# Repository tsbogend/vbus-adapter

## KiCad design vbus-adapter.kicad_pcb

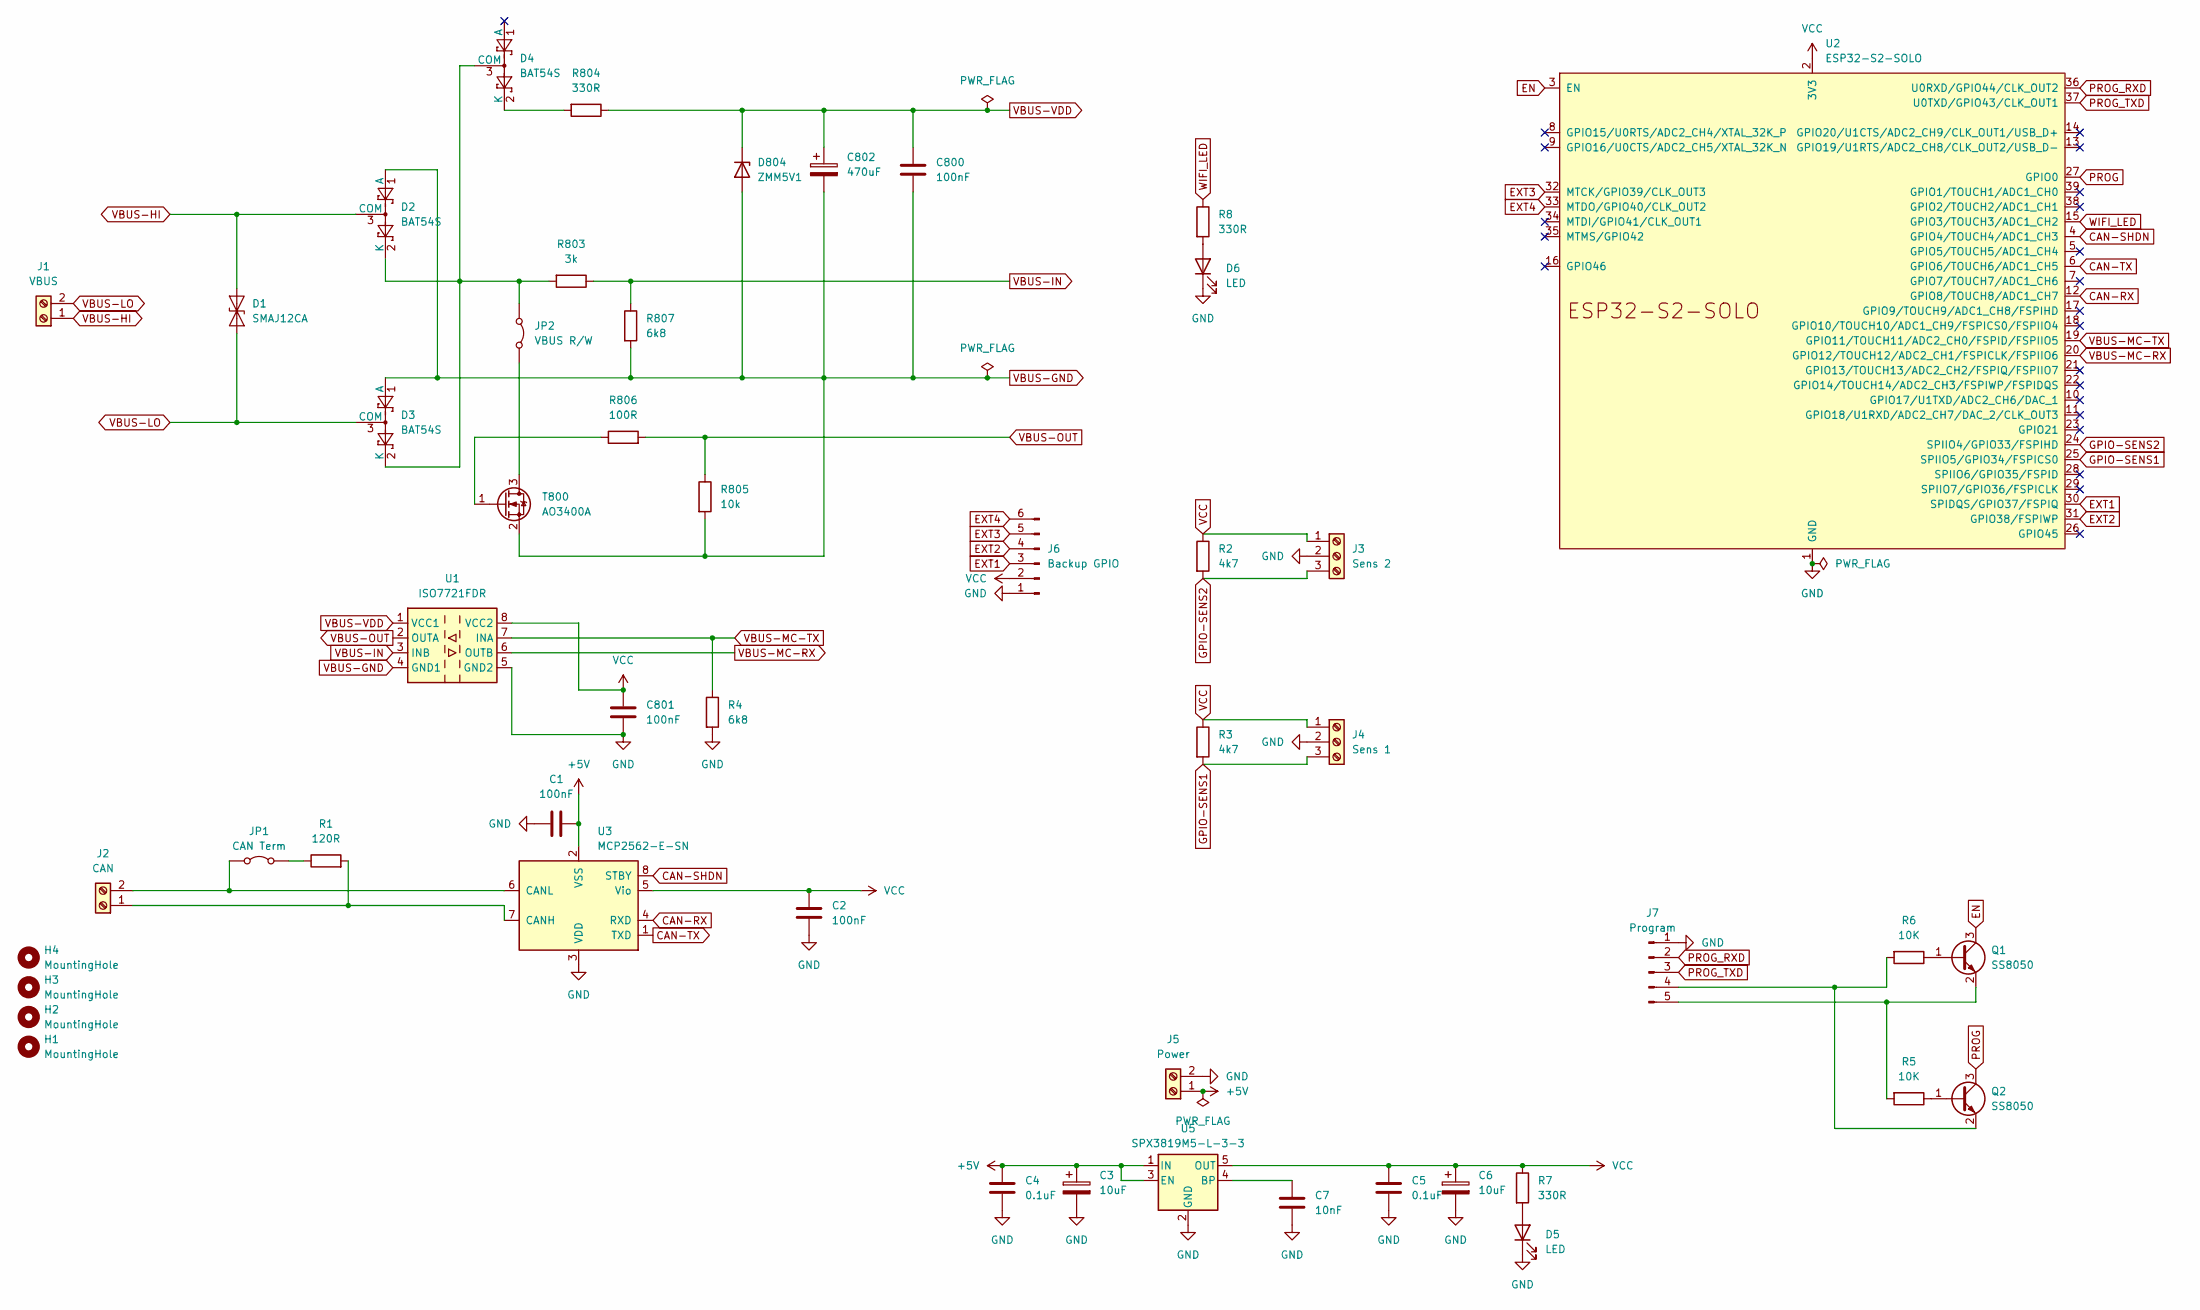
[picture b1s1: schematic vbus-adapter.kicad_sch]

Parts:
C1, C2, C800, C801: 100nF; C_0805_2012Metric_Pad1.18x1.45mm_HandSolder
C3, C6: 10uF; C_0805_2012Metric_Pad1.18x1.45mm_HandSolder
C4, C5: 0.1uF; C_0805_2012Metric_Pad1.18x1.45mm_HandSolder
C7: 10nF; C_0805_2012Metric_Pad1.18x1.45mm_HandSolder
C802: 470uF; CP_Elec_4x3.9
D1: SMAJ12CA; D_SMA
D2, D3, D4: BAT54S; SOT-23
D5, D6: LED; LED_0805_2012Metric_Pad1.15x1.40mm_HandSolder
D804: ZMM5V1; D_MiniMELF
H1, H2, H3, H4: MountingHole; MountingHole_3.2mm_M3_DIN965_Pad
J1: VBUS; TerminalBlock_Phoenix_MPT-0,5-2-2.54_1x02_P2.54mm_Horizontal
J2: CAN; TerminalBlock_Phoenix_MPT-0,5-2-2.54_1x02_P2.54mm_Horizontal
J3: Sens 2; TerminalBlock_Phoenix_MPT-0,5-3-2.54_1x03_P2.54mm_Horizontal
J4: Sens 1; TerminalBlock_Phoenix_MPT-0,5-3-2.54_1x03_P2.54mm_Horizontal
J5: Power; TerminalBlock_Phoenix_MPT-0,5-2-2.54_1x02_P2.54mm_Horizontal
J6: Backup GPIO; PinHeader_1x06_P2.54mm_Vertical
J7: Program; PinHeader_1x05_P2.54mm_Vertical
JP1: CAN Term; PinHeader_1x02_P2.54mm_Vertical
JP2: VBUS R/W; PinHeader_1x02_P2.54mm_Vertical
Q1, Q2: SS8050; SOT-23
R1: 120R; R_0805_2012Metric_Pad1.20x1.40mm_HandSolder
R2, R3: 4k7; R_0805_2012Metric_Pad1.20x1.40mm_HandSolder
R4, R807: 6k8; R_0805_2012Metric_Pad1.20x1.40mm_HandSolder
R5, R6: 10K; R_0805_2012Metric_Pad1.20x1.40mm_HandSolder
R7, R8, R804: 330R; R_0805_2012Metric_Pad1.20x1.40mm_HandSolder
R803: 3k; R_0805_2012Metric_Pad1.20x1.40mm_HandSolder
R805: 10k; R_0805_2012Metric_Pad1.20x1.40mm_HandSolder
R806: 100R; R_0805_2012Metric_Pad1.20x1.40mm_HandSolder
T800: AO3400A; SOT-23
U1: ISO7721FDR; SOIC-8_3.9x4.9mm_P1.27mm
U2: ESP32-S2-SOLO
U3: MCP2562-E-SN; SOIC-8_3.9x4.9mm_P1.27mm
U5: SPX3819M5-L-3-3; SOT-23-5

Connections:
+5V: C1.1, C3.1, C4.1, J5.1, U3.2 (VSS), U5.1 (IN), U5.3 (EN)
CAN-RX: U2.12 (GPIO8/TOUCH8/ADC1_CH7), U3.4 (RXD)
CAN-SHDN: U2.4 (GPIO4/TOUCH4/ADC1_CH3), U3.8 (STBY)
CAN-TX: U2.6 (GPIO6/TOUCH6/ADC1_CH5), U3.1 (TXD)
EN: Q1.3 (C), U2.3 (EN)
EXT1: J6.3, U2.30 (SPIDQS/GPIO37/FSPIQ)
EXT2: J6.4, U2.31 (GPIO38/FSPIWP)
EXT3: J6.5, U2.32 (MTCK/GPIO39/CLK_OUT3)
EXT4: J6.6, U2.33 (MTDO/GPIO40/CLK_OUT2)
GND: C1.2, C2.2, C3.2, C4.2, C5.2, C6.2, C7.2, C801.2, D5.1 (K), D6.1 (K), J3.2, J4.2, J5.2, J6.1, J7.1, R4.2, U1.5 (GND2), U2.1 (GND), U2.40 (GND), U2.41 (GND), U3.3 (VDD), U5.2 (GND)
GPIO-SENS1: J4.3, R3.2, U2.25 (SPIIO5/GPIO34/FSPICS0)
GPIO-SENS2: J3.3, R2.2, U2.24 (SPIIO4/GPIO33/FSPIHD)
unnamed: D2.2 (K), D3.2 (K), D4.3 (COM), JP2.1 (A), R803.2
unnamed: D4.2 (K), R804.2
unnamed: D5.2 (A), R7.2
unnamed: D6.2 (A), R8.2
unnamed: J2.1, R1.2, U3.7 (CANH)
unnamed: J2.2, JP1.1 (A), U3.6 (CANL)
unnamed: J7.4, Q2.2 (E), R6.2
unnamed: J7.5, Q1.2 (E), R5.2
unnamed: JP1.2 (B), R1.1
unnamed: JP2.2 (B), T800.3 (D)
unnamed: Q1.1 (B), R6.1
unnamed: Q2.1 (B), R5.1
unnamed: R806.1, T800.1 (G)
unnamed: C7.1, U5.4 (BP)
PROG: Q2.3 (C), U2.27 (GPIO0)
PROG_RXD: J7.2, U2.36 (U0RXD/GPIO44/CLK_OUT2)
PROG_TXD: J7.3, U2.37 (U0TXD/GPIO43/CLK_OUT1)
VBUS-GND: C800.2, C802.2, D2.1 (A), D3.1 (A), D804.2 (A), R805.2, R807.2, T800.2 (S), U1.4 (GND1)
VBUS-HI: D1.1 (A1), D2.3 (COM), J1.1
VBUS-IN: R803.1, R807.1, U1.3 (INB)
VBUS-LO: D1.2 (A2), D3.3 (COM), J1.2
VBUS-MC-RX: U1.6 (OUTB), U2.20 (GPIO12/TOUCH12/ADC2_CH1/FSPICLK/FSPIIO6)
VBUS-MC-TX: R4.1, U1.7 (INA), U2.19 (GPIO11/TOUCH11/ADC2_CH0/FSPID/FSPIIO5)
VBUS-OUT: R805.1, R806.2, U1.2 (OUTA)
VBUS-VDD: C800.1, C802.1, D804.1 (K), R804.1, U1.1 (VCC1)
VCC: C2.1, C5.1, C6.1, C801.1, J3.1, J4.1, J6.2, R2.1, R3.1, R7.1, U1.8 (VCC2), U2.2 (3V3), U3.5 (Vio), U5.5 (OUT)
WIFI_LED: R8.1, U2.15 (GPIO3/TOUCH3/ADC1_CH2)

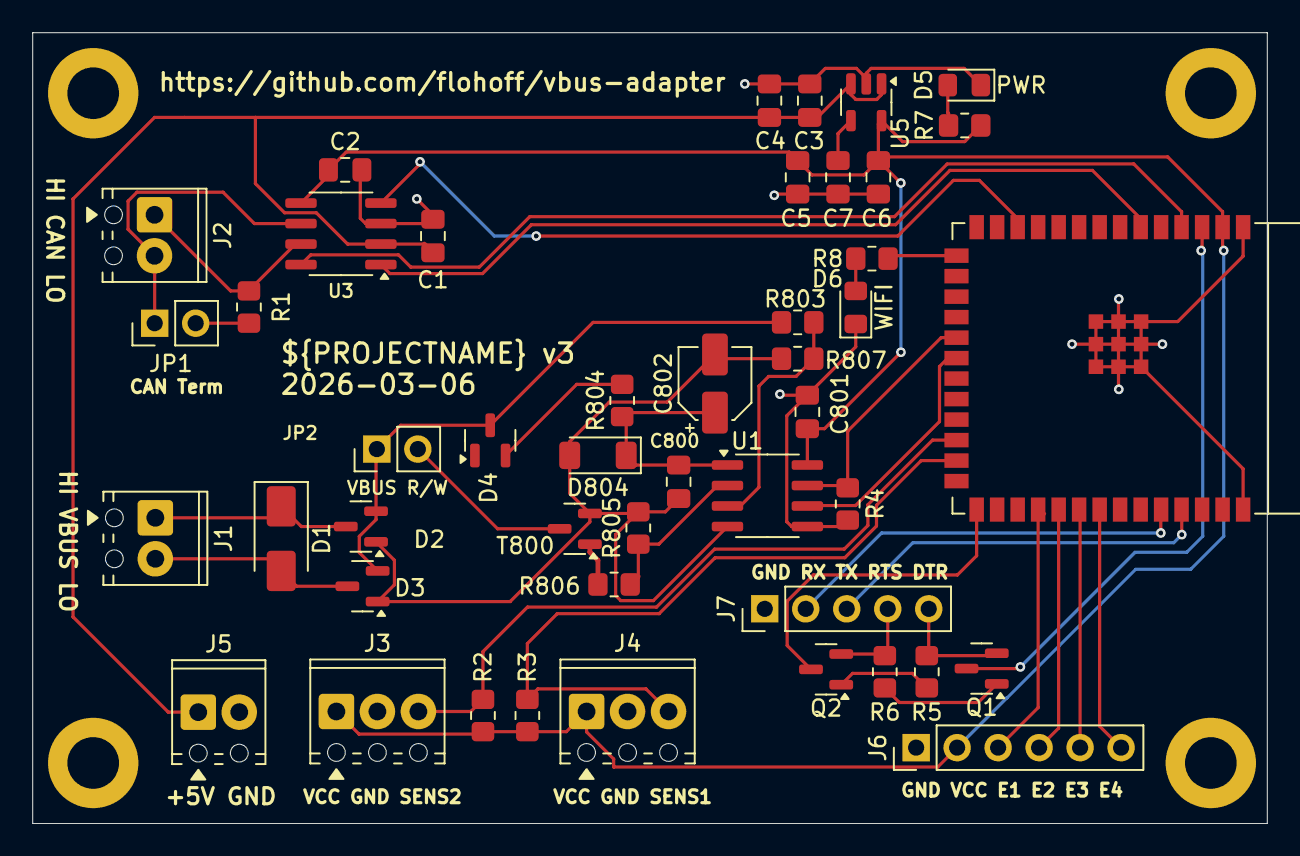
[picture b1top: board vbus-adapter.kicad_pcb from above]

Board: 2 copper layers, 76.5 x 49.0 mm, 50 parts (0 on the bottom side), 39 nets.

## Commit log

2026-01-22 Fix some issues
    - Use ISO7721FDR (Default Low output) so on disconnect of
    the ESP32 (Power loss) the VBUS will not be pulled to low
    e.g. bus disabled.
    - Add pull-down resistor to ISO input for TX
    - Add VBUS r/w jumper disconnecting the MOSFet drain from the VBUS
2026-03-05 Version 2
2026-03-06 Version 3 - Move GPIO for SENS, Add PWR/WIFI LED
